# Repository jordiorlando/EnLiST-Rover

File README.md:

EnLiST-Rover
============

EnLiST Rover modelled on the Curiosity Rover. The goal is to use it as a teaching platform for middle and high school students.

## Motor Controller
[Motor Controller Test Video](https://www.youtube.com/watch?v=swelm4EhzFY) demonstrating PC simulation and gamepad interface.

## Prototype Photos

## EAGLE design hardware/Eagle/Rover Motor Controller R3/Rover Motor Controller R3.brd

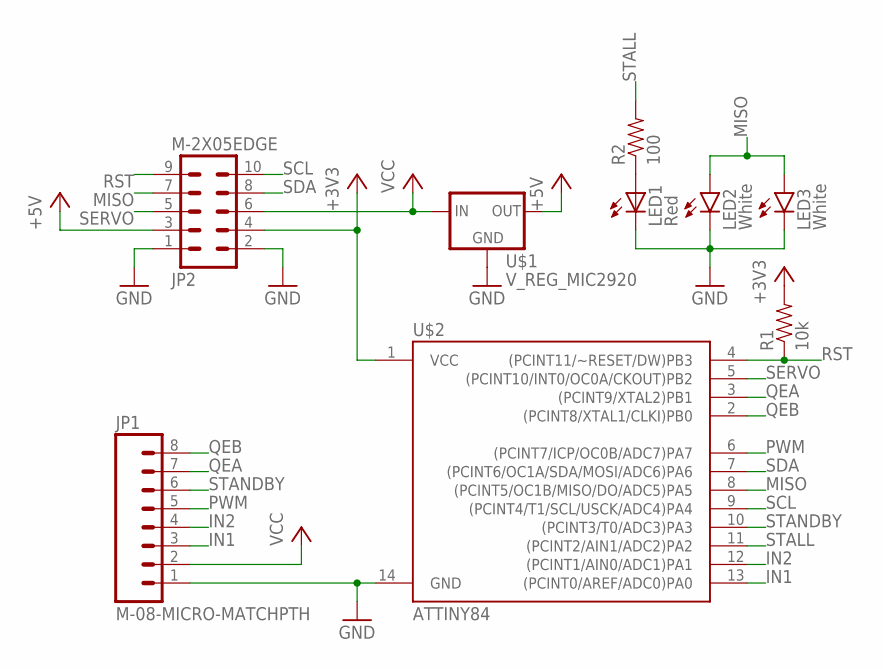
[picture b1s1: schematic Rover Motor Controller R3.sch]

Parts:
JP1: M-08-MICRO-MATCHPTH; M-08-MICRO-MATCH-PTH
JP2: M-2X05EDGE; M-2X05-0.1-EDGE
LED1: Red; SML0603
LED2, LED3: White; LED-SMD-RA
R1: 10k; R0603
R2: 100; R0603
U$1: V_REG_MIC2920; SOT223
U$2: ATTINY84; SO14

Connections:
+3V3: JP2.4, R1.2, U$2.1 (VCC)
+5V: JP2.3, U$1.3 (OUT)
GND: JP1.1, JP2.1, JP2.2, LED1.C, LED2.C, LED3.C, U$1.2 (GND), U$2.14 (GND)
IN1: JP1.3, U$2.13 ((PCINT0/AREF/ADC0)PA0)
IN2: JP1.4, U$2.12 ((PCINT1/AIN0/ADC1)PA1)
MISO: JP2.7, LED2.A, LED3.A, U$2.8 ((PCINT5/OC1B/MISO/DO/ADC5)PA5)
unnamed: LED1.A, R2.1
PWM: JP1.5, U$2.6 ((PCINT7/ICP/OC0B/ADC7)PA7)
QEA: JP1.7, U$2.3 ((PCINT9/XTAL2)PB1)
QEB: JP1.8, U$2.2 ((PCINT8/XTAL1/CLKI)PB0)
RST: JP2.9, R1.1, U$2.4 ((PCINT11/~RESET/DW)PB3)
SCL: JP2.10, U$2.9 ((PCINT4/T1/SCL/USCK/ADC4)PA4)
SDA: JP2.8, U$2.7 ((PCINT6/OC1A/SDA/MOSI/ADC6)PA6)
SERVO: JP2.5, U$2.5 ((PCINT10/INT0/OC0A/CKOUT)PB2)
STALL: R2.2, U$2.11 ((PCINT2/AIN1/ADC2)PA2)
STANDBY: JP1.6, U$2.10 ((PCINT3/T0/ADC3)PA3)
VCC: JP1.2, JP2.6, U$1.1 (IN)

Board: 2 copper layers, 9 parts (3 on the bottom side), 17 nets, no tracks yet.

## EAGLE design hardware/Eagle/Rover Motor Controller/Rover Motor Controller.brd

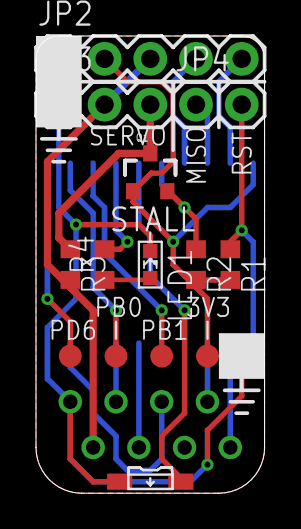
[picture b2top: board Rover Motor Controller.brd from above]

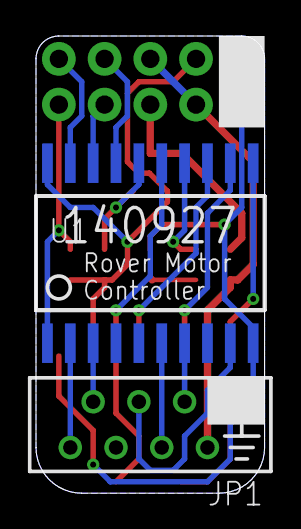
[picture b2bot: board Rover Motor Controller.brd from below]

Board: 2 copper layers, 12.7 x 25.4 mm, 17 parts (2 on the bottom side), 20 nets.

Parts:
JP1: M-08-MICRO-MATCHPTH; M-08-MICRO-MATCH-PTH
JP2: M-1X05PTH; M-1X05-0.1-PTH
JP3: M-1X03PTH; M-1X03-0.1-PTH
JP4: M-1X02PTH; M-1X02-0.1-PTH
LED1: Red; SML0603
LED2: White; LED-SMD-RA
Q1: MOSFET-NCHANNELBSS123LT1G; SOT23-3
R1, R2, R3: 10k; R0603
R4: 1k; R0603
TP1, TP2, TP3, TP4, TP5: TEST-POINT3X5; PAD.03X.05
U1: ATTINY2313A; SOP20W

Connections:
+3V3: JP2.2, Q1.1, R1.2, R2.2, TP4.P$1, U1.20
GND: JP1.1, JP2.1, JP3.1, LED1.C, LED2.C, TP5.P$1, U1.10
IN1: JP1.3, U1.7
IN2: JP1.4, U1.6
LAMP: LED2.A, U1.15
MISO: JP4.1, U1.18
unnamed: Q1.2, R2.1, U1.16
unnamed: LED1.A, R4.1
PB0: TP2.P$1, U1.12
PB1: TP1.P$1, U1.13
PD6: TP3.P$1, U1.11
PWM: JP1.5, U1.9
QEA: JP1.7, U1.3
QEB: JP1.8, U1.2
RST: JP4.2, R1.1, U1.1
SCL: JP2.5, U1.19
SDA: JP2.4, U1.17
SERVO: JP3.3, Q1.3, R3.1
STALL: R4.2, U1.14
VCC: JP1.2, JP2.3, JP3.2, R3.2

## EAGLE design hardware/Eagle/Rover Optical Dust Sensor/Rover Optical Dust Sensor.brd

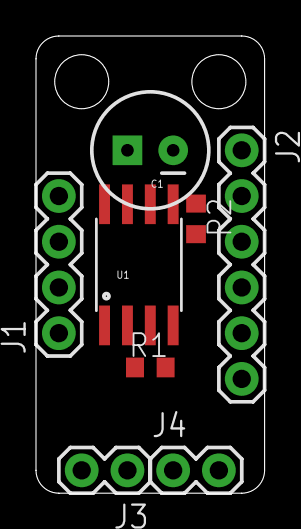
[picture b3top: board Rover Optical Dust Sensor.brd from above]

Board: 2 copper layers, 12.7 x 25.4 mm, 9 parts (1 on the bottom side), 10 nets, no tracks yet.

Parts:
C1: 220uF; CPOL-RADIAL-100UF-25V
J1: M-1X04-0.1-PTH
J2: M-1X06-0.1-PTH
J3, J4: M-1X02-0.1-PTH
R1: 10k; R0603
R2: 150; R0603
SJ1: JUMPER-PAD-3-2OF3_NC_BY_PASTE; PAD-JUMPER-3-2OF3_NC_BY_PASTE_YES_SILK_FULL_BOX
U1: Tiny85-20-SMT; SO08-EIAJ

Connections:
+3V3: J1.2, R1.2, SJ1.3, U1.8
+5V: J4.2, SJ1.1
GND: C1.2, J1.1, J2.2, J2.4, J4.1, U1.4
MISO: J3.2, U1.6
unnamed: J2.1, R2.1
RST: J3.1, R1.1, U1.1
SCL: J1.4, U1.7
SDA: J1.3, U1.5
VCC: C1.1, J2.6, R2.2, SJ1.2
VO: J2.5, U1.2

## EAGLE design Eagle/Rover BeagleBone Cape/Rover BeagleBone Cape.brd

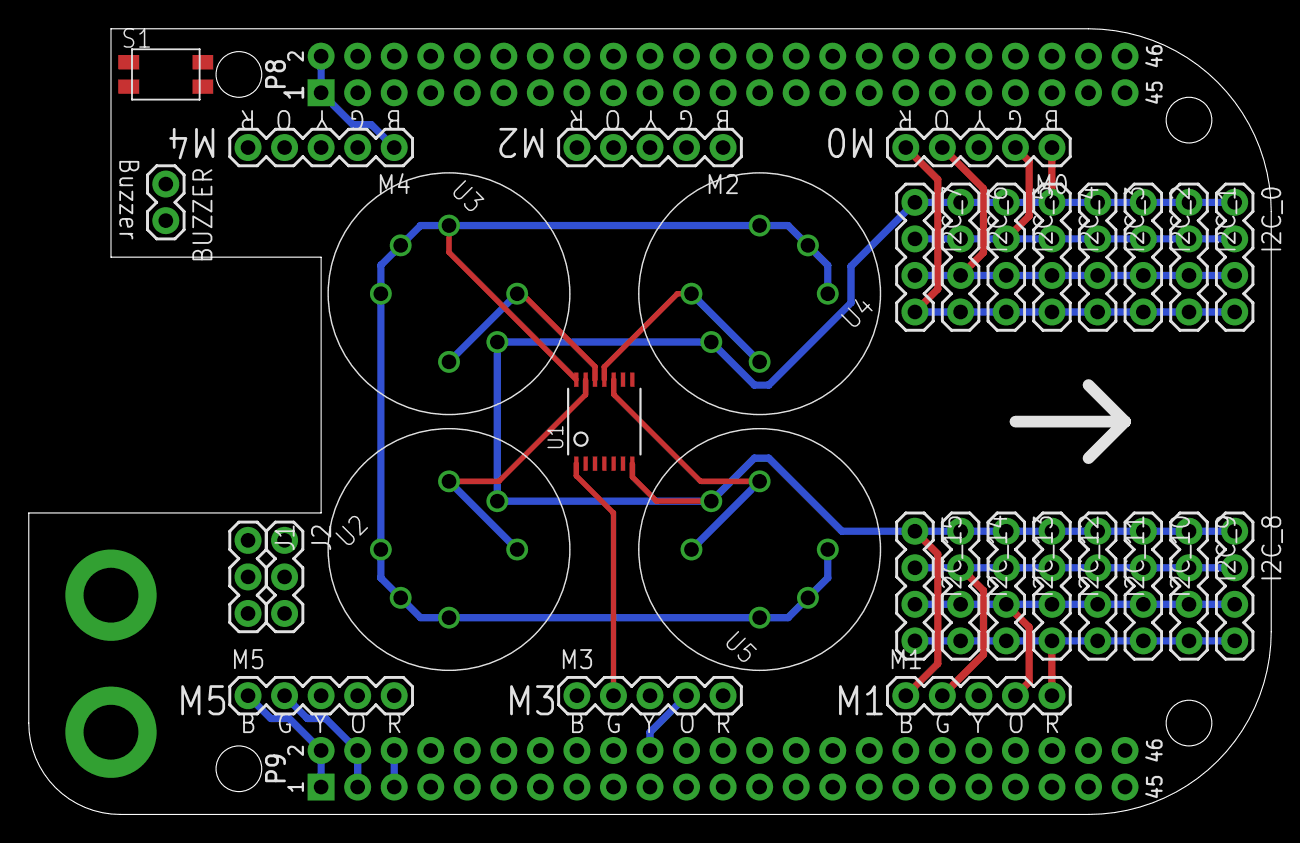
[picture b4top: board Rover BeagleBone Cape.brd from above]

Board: 2 copper layers, 86.4 x 54.6 mm, 32 parts (0 on the bottom side), 10 nets.

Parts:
BUZZER: M-1X02-0.1-PTH
I2C_0: IMU; M-1X04-0.1-PTH
I2C_1: Gas; M-1X04-0.1-PTH
I2C_2: Optical Dust; M-1X04-0.1-PTH
I2C_3: Temperature; M-1X04-0.1-PTH
I2C_4: Humidity; M-1X04-0.1-PTH
I2C_5: Barometric; M-1X04-0.1-PTH
I2C_6: Light; M-1X04-0.1-PTH
I2C_7, I2C_10, I2C_11, I2C_12, I2C_13, I2C_14, I2C_15: 1X04M-0.1-PTH; M-1X04-0.1-PTH
I2C_8: IR Temp; M-1X04-0.1-PTH
I2C_9: Color; M-1X04-0.1-PTH
J1, J2: M-1X03-0.1-PTH
M0, M1, M2, M3, M4, M5: M-1X05-0.1-PTH
S1: SWITCH-TACTILE-SMD
U1: TSSOP14
U2: Hydrogen; MQ-X
U3: Carbon Monoxide; MQ-X
U4: LPG; MQ-X
U5: Methane; MQ-X
U$1: BEAGLE_BONE_BLACK_CAPE

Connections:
+3V3: I2C_0.2, I2C_1.2, I2C_2.2, I2C_3.2, I2C_4.2, I2C_5.2, I2C_6.2, I2C_7.2, I2C_8.2, I2C_9.2, I2C_10.2, I2C_11.2, I2C_12.2, I2C_13.2, I2C_14.2, I2C_15.2, M0.2, M1.2, M2.2, M3.2, M4.2, M5.2, U1.1, U$1.P9.3, U$1.P9.4
+5V: J1.2, J2.2, U1.14, U2.A1, U2.A2, U2.HA, U3.A1, U3.A2, U3.HA, U4.A1, U4.A2, U4.HA, U5.A1, U5.A2, U5.HA, U$1.P9.5, U$1.P9.6
G1: U1.13, U2.B1, U2.B2
G2: U1.12, U3.B1, U3.B2
G3: U1.11, U4.B1, U4.B2
G4: U1.10, U5.B1, U5.B2
GND: I2C_0.1, I2C_1.1, I2C_2.1, I2C_3.1, I2C_4.1, I2C_5.1, I2C_6.1, I2C_7.1, I2C_8.1, I2C_9.1, I2C_10.1, I2C_11.1, I2C_12.1, I2C_13.1, I2C_14.1, I2C_15.1, J1.3, J2.3, M0.1, M1.1, M2.1, M3.1, M4.1, M5.1, U1.7, U2.HB, U3.HB, U4.HB, U5.HB, U$1.P8.1, U$1.P8.2, U$1.P9.1, U$1.P9.2, U$1.P9.43, U$1.P9.44, U$1.P9.45, U$1.P9.46
SCL: I2C_0.4, I2C_1.4, I2C_2.4, I2C_3.4, I2C_4.4, I2C_5.4, I2C_6.4, I2C_7.4, I2C_8.4, I2C_9.4, I2C_10.4, I2C_11.4, I2C_12.4, I2C_13.4, I2C_14.4, I2C_15.4, M0.5, M1.5, M2.5, M3.5, M4.5, M5.5, U$1.P9.19
SDA: I2C_0.3, I2C_1.3, I2C_2.3, I2C_3.3, I2C_4.3, I2C_5.3, I2C_6.3, I2C_7.3, I2C_8.3, I2C_9.3, I2C_10.3, I2C_11.3, I2C_12.3, I2C_13.3, I2C_14.3, I2C_15.3, M0.4, M1.4, M2.4, M3.4, M4.4, M5.4, U$1.P9.20
VCC: M0.3, M1.3, M2.3, M3.3, M4.3, M5.3

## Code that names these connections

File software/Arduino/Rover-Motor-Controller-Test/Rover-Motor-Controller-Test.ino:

#define IN1	0
#define IN2	1
#define STALL	2
#define STANDBY	3
#define LAMP	5
#define PWM	7
#define SERVO	8
#define QEA	9
#define QEB	10

void setup() {
  pinMode(IN1, OUTPUT);
  pinMode(IN2, OUTPUT);
  pinMode(STALL, OUTPUT);
  pinMode(STANDBY, OUTPUT);
  pinMode(LAMP, OUTPUT);
  pinMode(PWM, OUTPUT);
  pinMode(QEA, INPUT);
  pinMode(QEB, INPUT);
  
  digitalWrite(STANDBY, HIGH);
  digitalWrite(IN1, LOW);
  digitalWrite(IN2, HIGH);
  
  analogWrite(PWM, 63);
}

void loop() {
  /*
  digitalWrite(STALL, digitalRead(QEA));
  digitalWrite(LAMP, digitalRead(QEB));
  */
  
  
  for (uint8_t i = 0; i < 255; i++) {
    analogWrite(LAMP, i);
    //analogWrite(PWM, i / 4);
    delay(10);
  }
  
  for (uint8_t i = 255; i > 0; i--) {
    analogWrite(LAMP, i);
    //analogWrite(PWM, i / 4);
    delay(10);
  }
  
}

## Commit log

2014-10-02 Added gitignore
2014-10-02 Wiped gitignore
2014-10-02 Removed Mac Aliases
2014-10-02 Added PCB Design Files
    Added the WIP BBB cape and the completed motor controller PCB files
    under the Eagle directory.
2014-10-02 Added Inspiration!
2014-10-02 Added BOM
2014-10-07 Added BBB Basics
2014-10-16 New Motor Controller Revision
2014-10-31 Added preliminary motor controller code
    Added Arduino code and PCB revisions
2014-10-31 Revised code
2014-10-31 Added more motor controller code
2014-10-31 Started implementing PID code
2014-10-31 Added beaglebone test program
    The cpp files (and simple test page) for the WIP beaglebone test code
2014-10-31 Added preliminary roadmap
2014-11-04 I2C Improvements
    Added SMBus function wrappers to the I2C device class, made I2C
    read/write functions more general, added IRTempSensor as a simple
    example of an I2C device derived class.
2014-11-04 Add starter webapp using Polymer and Blockly
2014-11-04 Move resource files
2014-11-04 Add plans for future features
2014-11-05 Update Mission Control interface
2014-11-05 Update web references
2014-11-05 Fix markdown formatting
2014-11-05 Add website build instructions
2014-11-05 Revert "Fix markdown formatting"
    This reverts commit 764c32ac2538e8093651027d6a7bef5a42938642.
2014-11-06 Initial eagle files for several sensors
2014-11-06 Create gh-pages branch via GitHub
2014-11-06 Add LICENSE file via addalicense.com
2014-11-06 Add LICENSE file
    Code is licensed under MPL v2
2014-11-06 Add LICENSE file
    Mechanical design is licensed under CC BY-SA 4.0
2014-11-06 Add Mission Control
2014-11-06 Change name to Mission-Control
2014-11-06 Temporary fix for iframe sizing
    Temporary fix for iframe not taking up enough vertical space
2014-11-06 Fix content sizing
    Add "fit" attribute to content div
2014-11-06 Fix content sizing
    Add “fit” attribute to content div
2014-11-06 Reorganize repository
2014-11-06 Revert 04bcd0d..a5c9ea5
    This rolls back to commit 04bcd0dcca32584b946719aa940ac024b91c2dbb.
2014-11-09 Remove BOM
2014-11-09 Add LICENSE.txt
2014-11-19 Make compatible with Arduino IDE
2014-11-20 Add references
2014-11-20 Add ATtiny board descriptions
    Courtesy of http://highlowtech.org/?p=1695
2014-11-20 Add TinyWireS library
    https://github.com/rambo/TinyWire
2014-11-20 Motor Controller board revision
2014-11-20 Add PID library
    https://github.com/br3ttb/Arduino-PID-Library/
2014-11-20 Add servo library
    https://github.com/fri000/Servo8Bit
2014-11-20 Update libraries for ATtiny
2014-11-21 Move IMU resources
2014-11-21 Fully implement I2C register
2014-11-21 Fix Servo8Bit for ATtiny84
2014-11-21 Update Servo8Bit for ATtiny84
2014-11-22 Update dependencies
2014-12-09 Modify wheel struts
2014-12-10 Formatting
2014-12-10 Attiny84 compatibility (untested)
2014-12-10 Implement control register and motor control
2014-12-10 Add motor controller test program
2015-01-01 Add bogie suspension
2015-01-01 Begin defining inverse kinematics equations
2015-01-01 Create separate pages
2015-01-01 Add single page test app
2015-01-01 Update Bower dependencies
2015-01-01 Add Chart.js
2015-01-01 Fix branding
2015-01-01 Move styles to separate sheet
2015-01-01 Update to current state
2015-01-01 Chrome support
2015-01-01 Chrome compatibility
2015-01-02 Add flatiron director dependency
2015-01-02 Fix header coloring
2015-01-03 Add gamepad tester
2015-01-03 Ignore this update
2015-01-03 Fix dependencies
2015-01-03 Fix gitignore
2015-01-03 Simulate data analysis
2015-01-03 Simulate data visualization
2015-01-03 Add legends
2015-01-04 Import original HUB-ee 3D files
2015-01-04 Clean stats
2015-01-05 Prettification
2015-01-06 Added all changes to BBB software and rover control web pages.
2015-01-08 Add media files
2015-01-11 Add rover simulator in Processing
2015-01-11 Remove old, incorrect equations
2015-01-11 Tabify
2015-01-11 Add angle handling for wheels with a y-position of 0
2015-01-11 Add toggle for rover rotation display
2015-01-11 Modularization and various other improvements
2015-01-11 Make internal variables private
2015-01-12 Removed renamed genericSocket files, fixed bugs in streamSocket class.
2015-01-16 Adjust indentation
2015-01-16 Increase target size
2015-01-16 Use new Wheel API
2015-01-16 Under-the-hood improvements
2015-01-31 Begin work on motor controller R3
2015-01-31 Minor changes
2015-01-31 Begin porting mission control to Meteor
2015-01-31 Break everything (temporarily)
2015-02-22 Work on suspension and chassis
2015-02-26 Add bolts to body lid
2015-03-10 Tweak dimensions for more accurate 3D printing
2015-03-22 More changes I think
2015-03-23 Finally fix servo position calculations. Mostly. TODO: make less hacky
2015-03-23 Reorganize resource tree
2015-03-23 Nothing to see here, move along
2015-03-23 Fix servo control code w/ new library (untested)
2015-03-23 Beautify console
2015-03-24 Remove console, begin adding intuitive controls
2015-03-25 More prettification + objectification
2015-03-25 Pushed rover to its own object. TODO: comments
2015-03-25 Begin objectifying mast
2015-03-26 Moar OOP, also comments
    Switched Wheel class to a nested class (more concise/logical). Started
    commenting code.
2015-03-26 Add STELLArS logo
2015-03-28 Servo position is now from 0~180 deg
2015-03-28 Add serial port to control real motor controller
2015-03-28 Tweak comment style
2015-03-28 Make everything work
2015-03-28 Fix formatting and fix errors
2015-03-31 Changes for April launch
2015-03-31 More changes for April launch
2015-03-31 More changes. Revert to aea8f38 to get old models
2015-03-31 Final work for April print
2015-04-03 BBB changes
2015-04-08 Remove Roboto font (for now...)
2015-05-21 Normalize line endings
2016-02-16 Use 2-space tabs
2017-02-12 Add motor controller test
2017-02-12 Rename variables without hungarian notation, fix formatting
2017-02-17 Add photos to readme
2017-02-17 Set theme jekyll-theme-minimal and migrate Page Generator content
2017-02-17 Add motor controller R2 photos
2017-02-17 Add motor controller media
2017-05-05 Fix photo names

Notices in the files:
parts and their libraries:
SparkFun-Boards: Licensing: Creative Commons ShareAlike 4.0 International - https://creativecommons.org/licenses/by-sa/4.0
